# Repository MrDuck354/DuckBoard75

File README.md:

# DuckBoard 75

## Project Goals:
To create a basic 75% keyboard
By creating this keyboard, I will be learning how to 3D model/print on OnShape, how to create a PCB on KiCad and how to solder.

## Project Information
This project was inspired by a recent rabbit hole I went down in on youtube about custom keyboards, creators such as Glarses inspired me to get more into keyboards. Disappointed by my current HP office keyboard I wanted to get a mechanical keyboard but they're surprisingly expensive. I decided to design and build my own custom keyboard which would be a lot more affordable and a great learning opportunity for me. Also I just thought making my own keyboard would be a cool thing to flex on my friends...

The PCB was designed with the help of tutorials made by Joe Scotto on youtube, it doesn't feature anything cool, it's just a simple 75% keyboard PCB.
The case and top plate was made without any tutorials besides one to help me understand how OnShape works as I haven't used any of these softwares before. I want to make the case yellow or orange like a ducks bill so its more on theme for my name. 

My keyboard features 82 standard mechanical keys, its wired with an unpluggable wire but I could make it a permanent wire later on, I used a rp2042 because it seemed to be an option other people were suggesting on reddit, I chose Outemu switches because it was the cheapest option which was also reputable online and I decided on brown tactiles because they sound nice and tactile switches are probably closest to my current membrane keyboard but I don't know because I've never used a mechanical keyboard. I also thought about putting foam in between the bottom and the PCB which I may decided upon later once this project is approved and I get the parts (insert my decision here). There wasn't much thought behind my software choices, I chose OnShape because people online said it was good and I get it for free through my school and I chose KiCad because everyone said it was the best.

## Steps
Made a PCB on KiCad with an arduino nano RP2042 and switches, made the PCB first so that I can model the case around it. 

Made a top plate on OnShape using the PCB as a reference

Made a bottom case to fit everything and put it all together

Created the firmware using iNimbleSloth's tutorial on youtube https://www.youtube.com/watch?v=9bjp_LteX_Y
[Completed](duckboard_firmware)

Soldered the electronics together
(Not yet completed)

For more information on how I made these parts or how they fit together, check my [JOURNAL.md](JOURNAL.md) where I documented my design process.

## OnShape link
Click on the link below then copy and paste the link in a browser to go to OnShape

[OnShape Link](OnShapeLink.md)

Download the files in the link below if you want to edit or view them in another software
The assembly is too big to upload to GitHub so I had to compress it and can only add the .stl file and not the .step file. Unzip the .zip file and download the .stl file to view the case assembly.

[Case Files](DuckBoard_75_Case)

## Bill of Materials
[BOM.csv](DuckBoard%2075%20BOM%20-%20DuckBoard%2075%20BOM%20-%20Sheet1.csv)
| Item | Price (USD) | QTY | Purpose | Total + Shipping |
| --- | --- | --- | --- | --- |
| [PCB](https://cart.jlcpcb.com/quote?spm=jlcpcb.Public.2006) | $27.40 | 5 (minimum) | Electronics for keyboard |  |
| [Juidinto Hex Socket M2 Screws](https://www.aliexpress.com/item/1005004527586307.html?spm=a2g0o.detail.0.0.11c3fgvnfgvnbD&mp=1&pdp_npi=6%40dis%21USD%21USD+1.13%21USD+1.11%21%21USD+1.11%21%21%21%402103212317823526741237199ea06e%2112000029486656873%21ct%21US%217547000002%21%211%210%21&gatewayAdapt=usa2glo4itemAdapt) | $2.33 | 1 | To hold everything together |  |
| [PBT Pudding Keycaps](https://www.aliexpress.com/item/1005012018517535.html?spm=a2g0o.productlist.main.7.71954d54hVE3nP&algo_pvid=f8d263d8-107e-42fb-be14-7c2d645b0794&algo_exp_id=f8d263d8-107e-42fb-be14-7c2d645b0794-6&pdp_ext_f=%7B%22order%22%3A%2223%22%2C%22spu_best_type%22%3A%22price%22%2C%22eval%22%3A%221%22%2C%22fromPage%22%3A%22search%22%7D&pdp_npi=6%40dis%21USD%2120.35%215.56%21%21%21135.86%2137.15%21%402101e81117896765692928461e1387%2112000057315324355%21sea%21NZ%217985869037%21X%211%210%21n_tag%3A-29911%3Bd%3Af3154200%3Bm03_new_user%3A-29895%3BpisId%3A5000000213800337&curPageLogUid=qlyhQy7xRVpn&utparam-url=scene%3Asearch%7Cquery_from%3A%7Cx_object_id%3A1005012018517535%7C_p_origin_prod%3A) | $20.65 | 1 | Keycaps |  |
| [DUROCK Plate Mount Stabilizers](https://www.aliexpress.com/item/1005006528731543.html?spm=a2g0o.productlist.0.0.112352680K8Aiv&mp=1&pdp_npi=6%40dis%21USD%21USD+8.16%21USD+7.46%21%21USD+7.46%21%21%21%402103212317823524874202004ea06e%2112000037543723490%21ct%21US%217547000002%21%211%210%21&gatewayAdapt=usa2glo4itemAdapt) | $8.84 | 1 | Stabilizers |  |
| [1N4148 Diodes](https://www.aliexpress.com/item/1005002339916163.html?spm=a2g0o.productlist.main.4.6cb16ae2c2K9iQ&aem_p4p_detail=202607311717321159445797392080000109962&algo_pvid=60e80187-334d-4970-9369-da9bf1ee4b9f&algo_exp_id=60e80187-334d-4970-9369-da9bf1ee4b9f-3&pdp_ext_f=%7B%22order%22%3A%221282%22%2C%22eval%22%3A%221%22%2C%22fromPage%22%3A%22search%22%7D&pdp_npi=6%40dis%21USD%210.89%210.87%21%21%210.89%210.87%21%402101de2517855434524457575e0cf2%2112000020175180916%21sea%21NZ%217985869037%21ABX%211%210%21n_tag%3A-29910%3Bd%3Af3154200%3Bm03_new_user%3A-29895&curPageLogUid=11r81NCdmT7s&utparam-url=scene%3Asearch%7Cquery_from%3A%7Cx_object_id%3A1005002339916163%7C_p_origin_prod%3A&search_p4p_id=202607311717321159445797392080000109962_1) | $0.87 | 1 | to control flow of electricity |  |
| [Outemu Tactile Brown Switches](https://www.aliexpress.com/item/1005004285423123.html?spm=a2g0o.productlist.main.11.2f361b6e73HJZu&algo_pvid=a090be33-1bfd-4105-8713-c38f03b5d6f4&algo_exp_id=a090be33-1bfd-4105-8713-c38f03b5d6f4-10&pdp_ext_f=%7B%22order%22%3A%2213737%22%2C%22spu_best_type%22%3A%22price%22%2C%22eval%22%3A%221%22%2C%22fromPage%22%3A%22search%22%7D&pdp_npi=6%40dis%21USD%212.87%210.99%21%21%212.87%210.99%21%402101e7a317855436822738413e0d41%2112000028628937373%21sea%21NZ%217985869037%21ABX%211%210%21n_tag%3A-29910%3Bd%3Af3154200%3Bm03_new_user%3A-29895%3BpisId%3A5000000210976560&curPageLogUid=kVSF8tEkUPWA&utparam-url=scene%3Asearch%7Cquery_from%3A%7Cx_object_id%3A1005004285423123%7C_p_origin_prod%3A) | $3.53 | 90pcs | switches |  |
| [RP2040 PICO Raspberry Pi Microcontroller](https://www.aliexpress.com/item/1005010706615847.html?spm=a2g0o.detail.0.0.32cafqdcfqdcYI&mp=1&sourceType=570&pdp_npi=6%40dis%21USD%21USD+5.65%21USD+1.76%21%21USD+1.76%21%21%21%402101c4ea17896769891305848e0f2e%2112000053252715800%21ct%21NZ%217985869037%21%211%210%21&pdp_ext_f=%7B%22cart2PdpParams%22%3A%7B%22sourceType%22%3A%22570%22%2C%22cartSource%22%3A%22main%22%7D%7D) | $2.64 | 1 | to control everything |  |
| [Solder Wire](https://www.aliexpress.com/item/1005008618276811.html?spm=a2g0o.detail.0.0.52389B1b9B1bxh&mp=1&sourceType=570&pdp_npi=6%40dis%21USD%21USD+3.51%21USD+1.10%21%21USD+1.10%21%21%21%402101c4ea17896770146086591e0f2e%2112000045972728168%21ct%21NZ%217985869037%21%211%210%21&pdp_ext_f=%7B%22cart2PdpParams%22%3A%7B%22sourceType%22%3A%22570%22%2C%22cartSource%22%3A%22main%22%7D%7D) | $1.32 | 1 | to connect electronics |  |
| [3D printing costs](https://www.wcl.govt.nz/services/technology/makerspace/#costs)| $20 | 1 | to create the case| |
| AliExpress Shipping (No link to shipping costs) | $6.50 |  | To get the items |  |
| JLCPCB Shipping (No link to shipping costs) | $20.69 |  | To get the PCB |  |
| Total Cost |  |  |  | $113.89 |

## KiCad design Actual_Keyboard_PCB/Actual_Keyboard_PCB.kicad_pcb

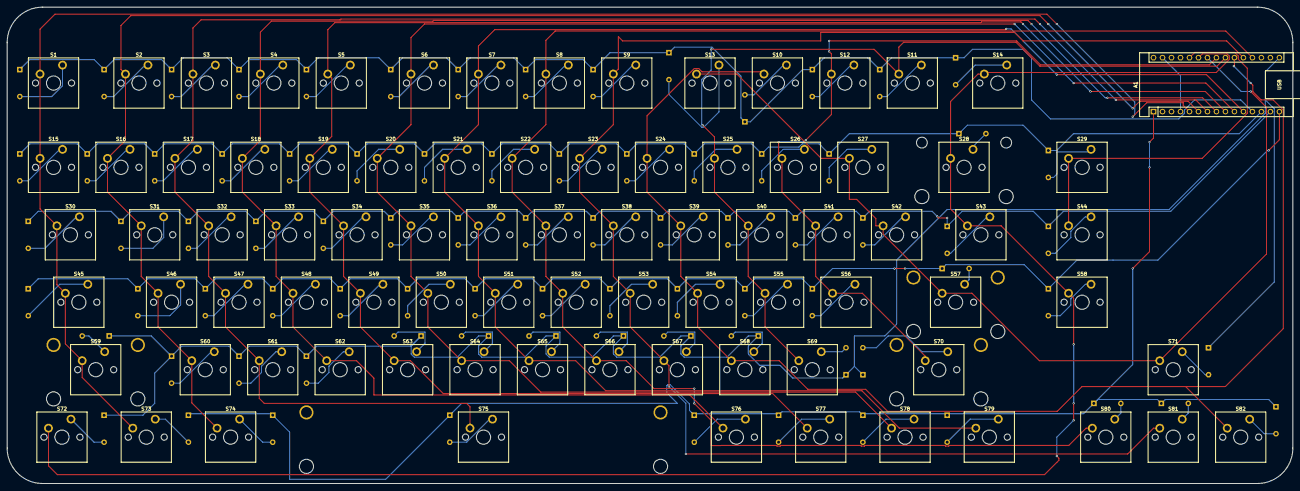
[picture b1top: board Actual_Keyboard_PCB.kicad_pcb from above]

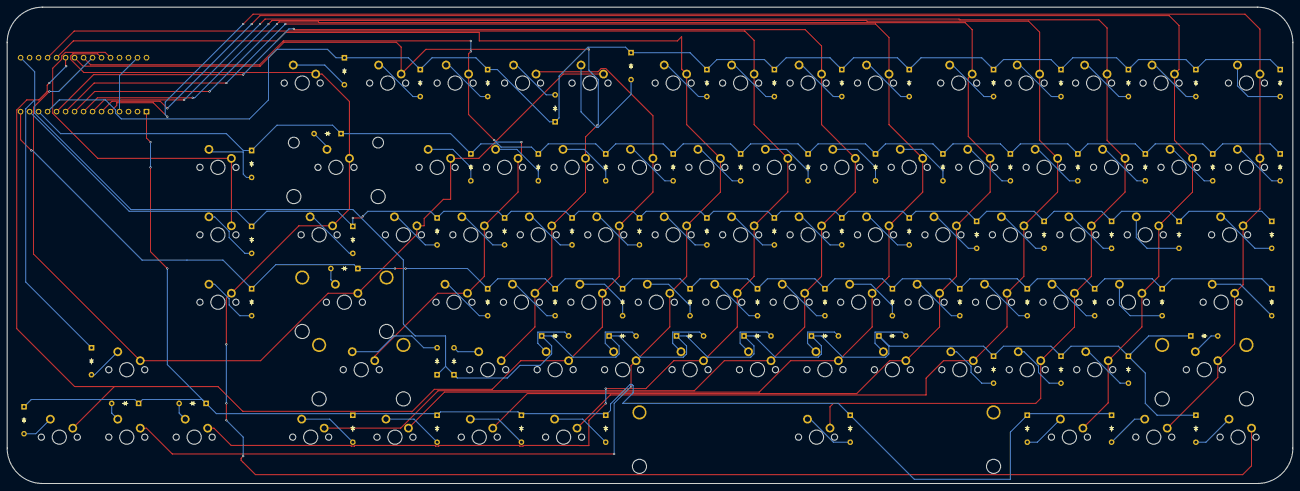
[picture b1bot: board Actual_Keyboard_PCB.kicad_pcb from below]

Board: 2 copper layers, 363.1 x 134.5 mm, 170 parts (82 on the bottom side), 104 nets.

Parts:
A1: Arduino_Nano_RP2040_Connect; Arduino_Nano
D1, D2, D3, D4, D5, D6, D7, D8, D9, D10, D11, D12, D13, D14, D15, D16, D17, D18, D19, D20, D21, D22, D23, D24, D25, D26, D27, D28, D29, D30, D31, D32, D33, D34, D35, D36, D37, D38, D39, D40, D41, D42, D43, D44, D45, D46, D47, D48, D49, D50, D51, D52, D53, D54, D55, D56, D57, D58, D59, D60, D61, D62, D63, D64, D65, D66, D67, D68, D69, D70, D71, D72, D73, D74, D75, D76, D77, D78, D79, D80, D81, D82: Diode_DO-35
S1, S2, S3, S4, S5, S6, S7, S8, S9, S10, S11, S12, S13, S14, S15, S16, S17, S18, S19, S20, S21, S22, S23, S24, S25, S26, S27, S29, S31, S32, S33, S34, S35, S36, S37, S38, S39, S40, S41, S42, S44, S46, S47, S48, S49, S50, S51, S52, S53, S54, S55, S56, S58, S60, S61, S62, S63, S64, S65, S66, S67, S68, S69, S71, S80, S81, S82: MX_PCB_1.00u
S28: MX_PCB_2.00u
S30, S43: MX_PCB_1.50u
S45: MX_PCB_1.75u
S57, S59: MX_PCB_2.25u
S70: MX_PCB_2.75u
S72, S73, S74, S76, S77, S78, S79: MX_PCB_1.25u
S75: MX_PCB_6.25u
S83, S84: MX_stab; STAB_MX_P_2.25u
S85: MX_stab; STAB_MX_P_2.75u
S86: MX_stab; STAB_MX_2u
S87: MX_stab; STAB_MX_P_6.25u

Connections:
/Column 0: A1.5 (D2), S1.1, S15.1, S30.1, S45.1, S59.1, S73.1
/Column 1: A1.6 (D3), S2.1, S16.1, S31.1, S46.1, S60.1, S74.1
/Column 2: A1.7 (D4), S3.1, S17.1, S32.1, S47.1, S61.1, S75.1
/Column 3: A1.8 (D5), S4.1, S18.1, S33.1, S48.1, S62.1, S76.1
/Column 4: A1.9 (D6), S5.1, S19.1, S34.1, S49.1, S63.1, S77.1
/Column 5: A1.10 (D7), S6.1, S20.1, S35.1, S50.1, S64.1, S78.1
/Column 6: A1.11 (D8), S7.1, S21.1, S36.1, S51.1, S65.1, S79.1
/Column 7: A1.19 (A0), S8.1, S22.1, S37.1, S52.1, S66.1, S80.1
/Column 8: A1.20 (A1), S9.1, S23.1, S38.1, S53.1, S67.1, S81.1
/Column 9: A1.21 (A2), S10.1, S24.1, S39.1, S54.1, S68.1, S82.1
/Column 10: A1.22 (A3), S11.1, S25.1, S40.1, S55.1, S69.1
/Column 11: A1.23 (SDA/A4), S12.1, S26.1, S41.1, S56.1, S70.1
/Column 12: A1.24 (SCL/A5), S13.1, S27.1, S42.1, S57.1, S71.1
/Column 13: A1.25 (A6), S14.1, S28.1, S43.1, S58.1, S72.1
/Column 14: A1.26 (A7), S29.1, S44.1
/Row 0: A1.12 (D9), D1.1 (K), D2.1 (K), D3.1 (K), D4.1 (K), D5.1 (K), D6.1 (K), D7.1 (K), D8.1 (K), D9.1 (K), D10.1 (K), D11.1 (K), D12.1 (K), D13.1 (K), D14.1 (K)
/Row 1: A1.13 (D10/CS), D15.1 (K), D16.1 (K), D17.1 (K), D18.1 (K), D19.1 (K), D20.1 (K), D21.1 (K), D22.1 (K), D23.1 (K), D24.1 (K), D25.1 (K), D26.1 (K), D27.1 (K), D28.1 (K), D29.1 (K)
/Row 2: A1.14 (D11/COPI), D30.1 (K), D31.1 (K), D32.1 (K), D33.1 (K), D34.1 (K), D35.1 (K), D36.1 (K), D37.1 (K), D38.1 (K), D39.1 (K), D40.1 (K), D41.1 (K), D42.1 (K), D43.1 (K), D44.1 (K)
/Row 3: A1.15 (D12/CIPO), D45.1 (K), D46.1 (K), D47.1 (K), D48.1 (K), D49.1 (K), D50.1 (K), D51.1 (K), D52.1 (K), D53.1 (K), D54.1 (K), D55.1 (K), D56.1 (K), D57.1 (K), D58.1 (K)
/Row 4: A1.16 (D13/SCK), D59.1 (K), D60.1 (K), D61.1 (K), D62.1 (K), D63.1 (K), D64.1 (K), D65.1 (K), D66.1 (K), D67.1 (K), D68.1 (K), D69.1 (K), D70.1 (K), D71.1 (K), D72.1 (K)
/Row 5: A1.1 (D1/TX), D73.1 (K), D74.1 (K), D75.1 (K), D76.1 (K), D77.1 (K), D78.1 (K), D79.1 (K), D80.1 (K), D81.1 (K), D82.1 (K)
unnamed: A1.4 (GND), A1.29 (GND)
unnamed: D1.2 (A), S1.2
unnamed: D2.2 (A), S2.2
unnamed: D3.2 (A), S3.2
unnamed: D4.2 (A), S4.2
unnamed: D5.2 (A), S5.2
unnamed: D6.2 (A), S6.2
unnamed: D7.2 (A), S7.2
unnamed: D8.2 (A), S8.2
unnamed: D9.2 (A), S9.2
unnamed: D10.2 (A), S10.2
unnamed: D11.2 (A), S11.2
unnamed: D12.2 (A), S12.2
unnamed: D13.2 (A), S13.2
unnamed: D14.2 (A), S14.2
unnamed: D15.2 (A), S15.2
unnamed: D16.2 (A), S16.2
unnamed: D17.2 (A), S17.2
unnamed: D18.2 (A), S18.2
unnamed: D19.2 (A), S19.2
unnamed: D20.2 (A), S20.2
unnamed: D21.2 (A), S21.2
unnamed: D22.2 (A), S22.2
unnamed: D23.2 (A), S23.2
unnamed: D24.2 (A), S24.2
unnamed: D25.2 (A), S25.2
unnamed: D26.2 (A), S26.2
unnamed: D27.2 (A), S27.2
unnamed: D28.2 (A), S28.2
unnamed: D29.2 (A), S29.2
unnamed: D30.2 (A), S30.2
unnamed: D31.2 (A), S31.2
unnamed: D32.2 (A), S32.2
unnamed: D33.2 (A), S33.2
unnamed: D34.2 (A), S34.2
unnamed: D35.2 (A), S35.2
unnamed: D36.2 (A), S36.2
unnamed: D37.2 (A), S37.2
unnamed: D38.2 (A), S38.2
unnamed: D39.2 (A), S39.2
unnamed: D40.2 (A), S40.2
unnamed: D41.2 (A), S41.2
unnamed: D42.2 (A), S42.2
unnamed: D43.2 (A), S43.2
unnamed: D44.2 (A), S44.2
unnamed: D45.2 (A), S45.2
unnamed: D46.2 (A), S46.2
unnamed: D47.2 (A), S47.2
unnamed: D48.2 (A), S48.2
unnamed: D49.2 (A), S49.2
unnamed: D50.2 (A), S50.2
unnamed: D51.2 (A), S51.2
unnamed: D52.2 (A), S52.2
unnamed: D53.2 (A), S53.2
unnamed: D54.2 (A), S54.2
unnamed: D55.2 (A), S55.2
unnamed: D56.2 (A), S56.2
unnamed: D57.2 (A), S57.2
unnamed: D58.2 (A), S58.2
unnamed: D59.2 (A), S59.2
unnamed: D60.2 (A), S60.2
unnamed: D61.2 (A), S61.2
unnamed: D62.2 (A), S62.2
unnamed: D63.2 (A), S63.2
unnamed: D64.2 (A), S64.2
unnamed: D65.2 (A), S65.2
unnamed: D66.2 (A), S66.2
unnamed: D67.2 (A), S67.2
unnamed: D68.2 (A), S68.2
unnamed: D69.2 (A), S69.2
unnamed: D70.2 (A), S70.2
unnamed: D71.2 (A), S71.2
unnamed: D72.2 (A), S72.2
unnamed: D73.2 (A), S73.2
unnamed: D74.2 (A), S74.2
unnamed: D75.2 (A), S75.2
unnamed: D76.2 (A), S76.2
unnamed: D77.2 (A), S77.2
unnamed: D78.2 (A), S78.2
unnamed: D79.2 (A), S79.2
unnamed: D80.2 (A), S80.2
unnamed: D81.2 (A), S81.2
unnamed: D82.2 (A), S82.2

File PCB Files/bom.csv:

Designator,Footprint,Quantity,Value,LCSC Part #
A1,Arduino_Nano,1,Arduino_Nano_RP2040_Connect,
"D1, D10, D11, D12, D13, D14, D15, D16, D17, D18, D19, D2, D20, D21, D22, D23, D24, D25, D26, D27, D28, D29, D3, D30, D31, D32, D33, D34, D35, D36, D37, D38, D39, D4, D40, D41, D42, D43, D44, D45, D46, D47, D48, D49, D5, D50, D51, D52, D53, D54, D55, D56, D57, D58, D59, D6, D60, D61, D62, D63, D64, D65, D66, D67, D68, D69, D7, D70, D71, D72, D73, D74, D75, D76, D77, D78, D79, D8, D80, D81, D82, D9",Diode_DO-35,82,~,
"S1, S10, S11, S12, S13, S14, S15, S16, S17, S18, S19, S2, S20, S21, S22, S23, S24, S25, S26, S27, S29, S3, S31, S32, S33, S34, S35, S36, S37, S38, S39, S4, S40, S41, S42, S44, S46, S47, S48, S49, S5, S50, S51, S52, S53, S54, S55, S56, S58, S6, S60, S61, S62, S63, S64, S65, S66, S67, S68, S69, S7, S71, S8, S80, S81, S82, S9",MX_PCB_1.00u,67,~,
S28,MX_PCB_2.00u,1,~,
"S30, S43",MX_PCB_1.50u,2,~,
S45,MX_PCB_1.75u,1,~,
"S57, S59",MX_PCB_2.25u,2,~,
S70,MX_PCB_2.75u,1,~,
"S72, S73, S74, S76, S77, S78, S79",MX_PCB_1.25u,7,~,
S75,MX_PCB_6.25u,1,~,
"S83, S84",STAB_MX_P_2.25u,2,MX_stab,
S85,STAB_MX_P_2.75u,1,MX_stab,
S86,STAB_MX_2u,1,MX_stab,
S87,STAB_MX_P_6.25u,1,MX_stab,
